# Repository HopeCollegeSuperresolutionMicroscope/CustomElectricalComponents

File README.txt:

#README

This Directory Serves To Store directions and specifications about electrical components of the microscope setup.

IMPORTANT Point about Schematics and EagleCAD:

	Schematics were created in EagleCAD free version.  These schematics make use of 3rd party libraries provided
        by sites like Element14 and handdrawn library parts based off of datasheets when not found.

	Opening a Schematic In EagleCAD:

		Since the free version of EagleCAD seems to limit all projects to the specific eagle/ folder designated
		 by the program on Install, it is recommended to move the schematic to this directory if intending to do 
		 work on the underlying schematic or pre-Gerber pcb board layout.

		In order to have access to the libraries, from the Eagle Control Panel: 
				Right click Libraries -> Library Manager
				Upper left Tab -> Available
				Browse -> Search for each library in EagleLibraries
				If the library is new it will be added in the Available dialog
				Click on the desired library and click Use button
				You should now see the library in the In Use Tab

Directory Layout:
	|
	|
	| ------- EagleLibraries/
	|		|	:Since Schematics were created in EagleCAD (freeware edition), additional libraries are housed here
	|		|
	|		|
	|		| ------- 3rdParty/ 
	|		|		: Part libraries that were imported from 3rd Party distributors.  See About.txt if wanting to look up revisions.
	|		|
	|		|
	|		| ------- HandCreated/
	|				: Parts that were created from Manufacturer DataSheets by individuals.  
	|				   Add the file name to Confirmed.txt when a pcb footprint has been used and verified.
	|
	|
	| ------- USB_TO_ILDA_Adapter/ 
	|		|	: Electronics for using ILDA device as a laser illumination source
	|		|
	|		|
	|		| ------- (Version) /
	|				|	:See About.txt for Version Different highlights
	|				|
	|				|
	|				| ------- Schematics/
	|				|		: Electrical Connection Schematics
	|				|
	|				|
	|				| ------- Gerber/
	|				|		: Gerber Files for PCBs that have been proven 
	|				|
	|				|
	|				| ------ DataSheets/
	|						: DataSheets Related to important components (ICs at the very least)
	|				
	|
	| ------ USB_TO_RS485_Connection/
	|		|	:Electronic connector and connections for RS-485 Comm with OrientalMotors CRPK
	|		|
	|		|
	|		| ------ Schematics/
	|		|		: Electrical Connections (Since this is a non-standard connection)
	|		|
	|		|
	|		| ------ DataSheets/
	|		|		: DataSheets related to important Components (motor controller and USB adapter)
	|		|
	|		|
	|		| ------ Figures/
	|				: Explanations for adapting the non-standard connection
	|		
	|
	| ------ Power_Supply/
			|	:Electrical connections for using Wall Power to provide stable voltage to OrientalMotors CRPK
			|
			|
			| ------ Schematics/
			|		: Electrical Connections (For pins to terminals etc.)
			|
			|
			| ------ DataSheets/ 
			|		: DataSheets related to important components
			|
			|
			| ------ Figures/
					:Explanation for making connections if there is a difficulty

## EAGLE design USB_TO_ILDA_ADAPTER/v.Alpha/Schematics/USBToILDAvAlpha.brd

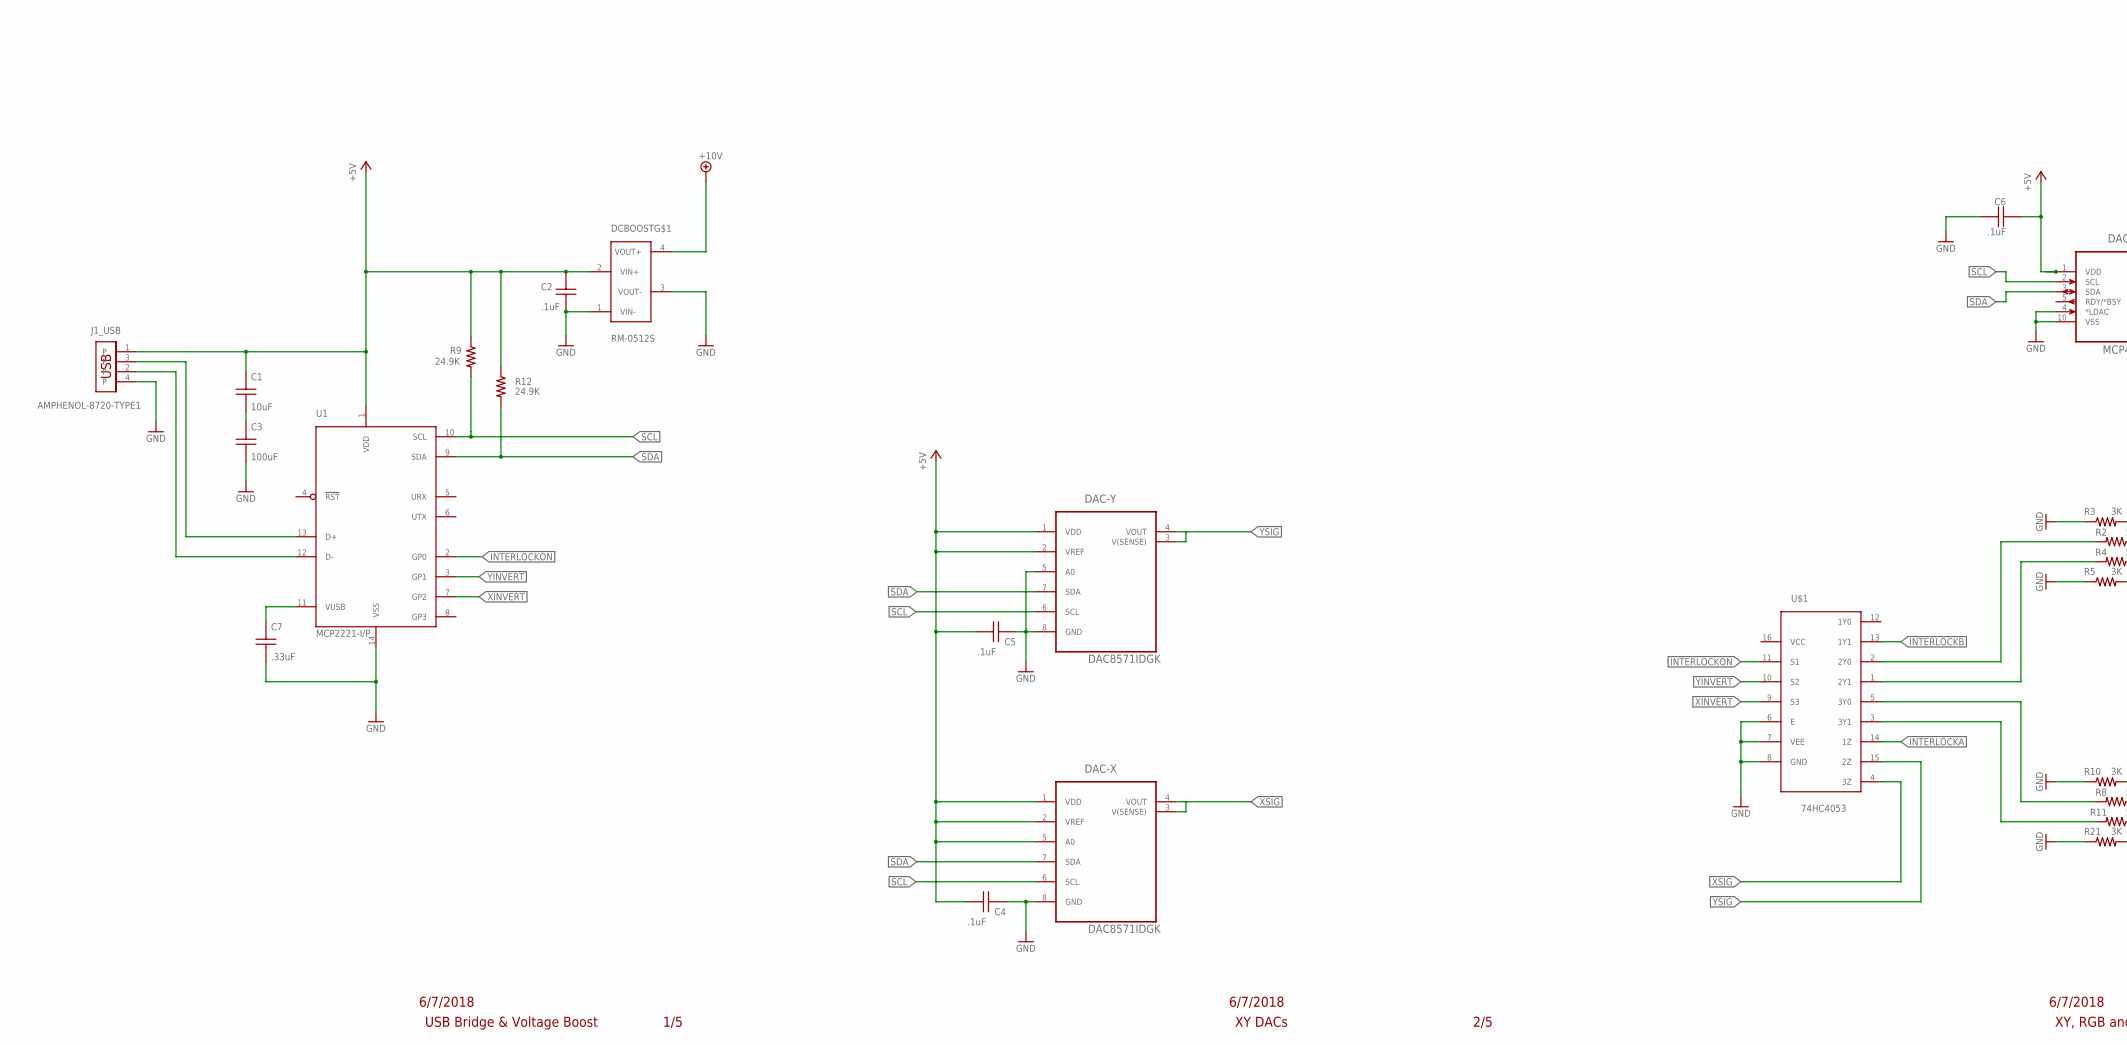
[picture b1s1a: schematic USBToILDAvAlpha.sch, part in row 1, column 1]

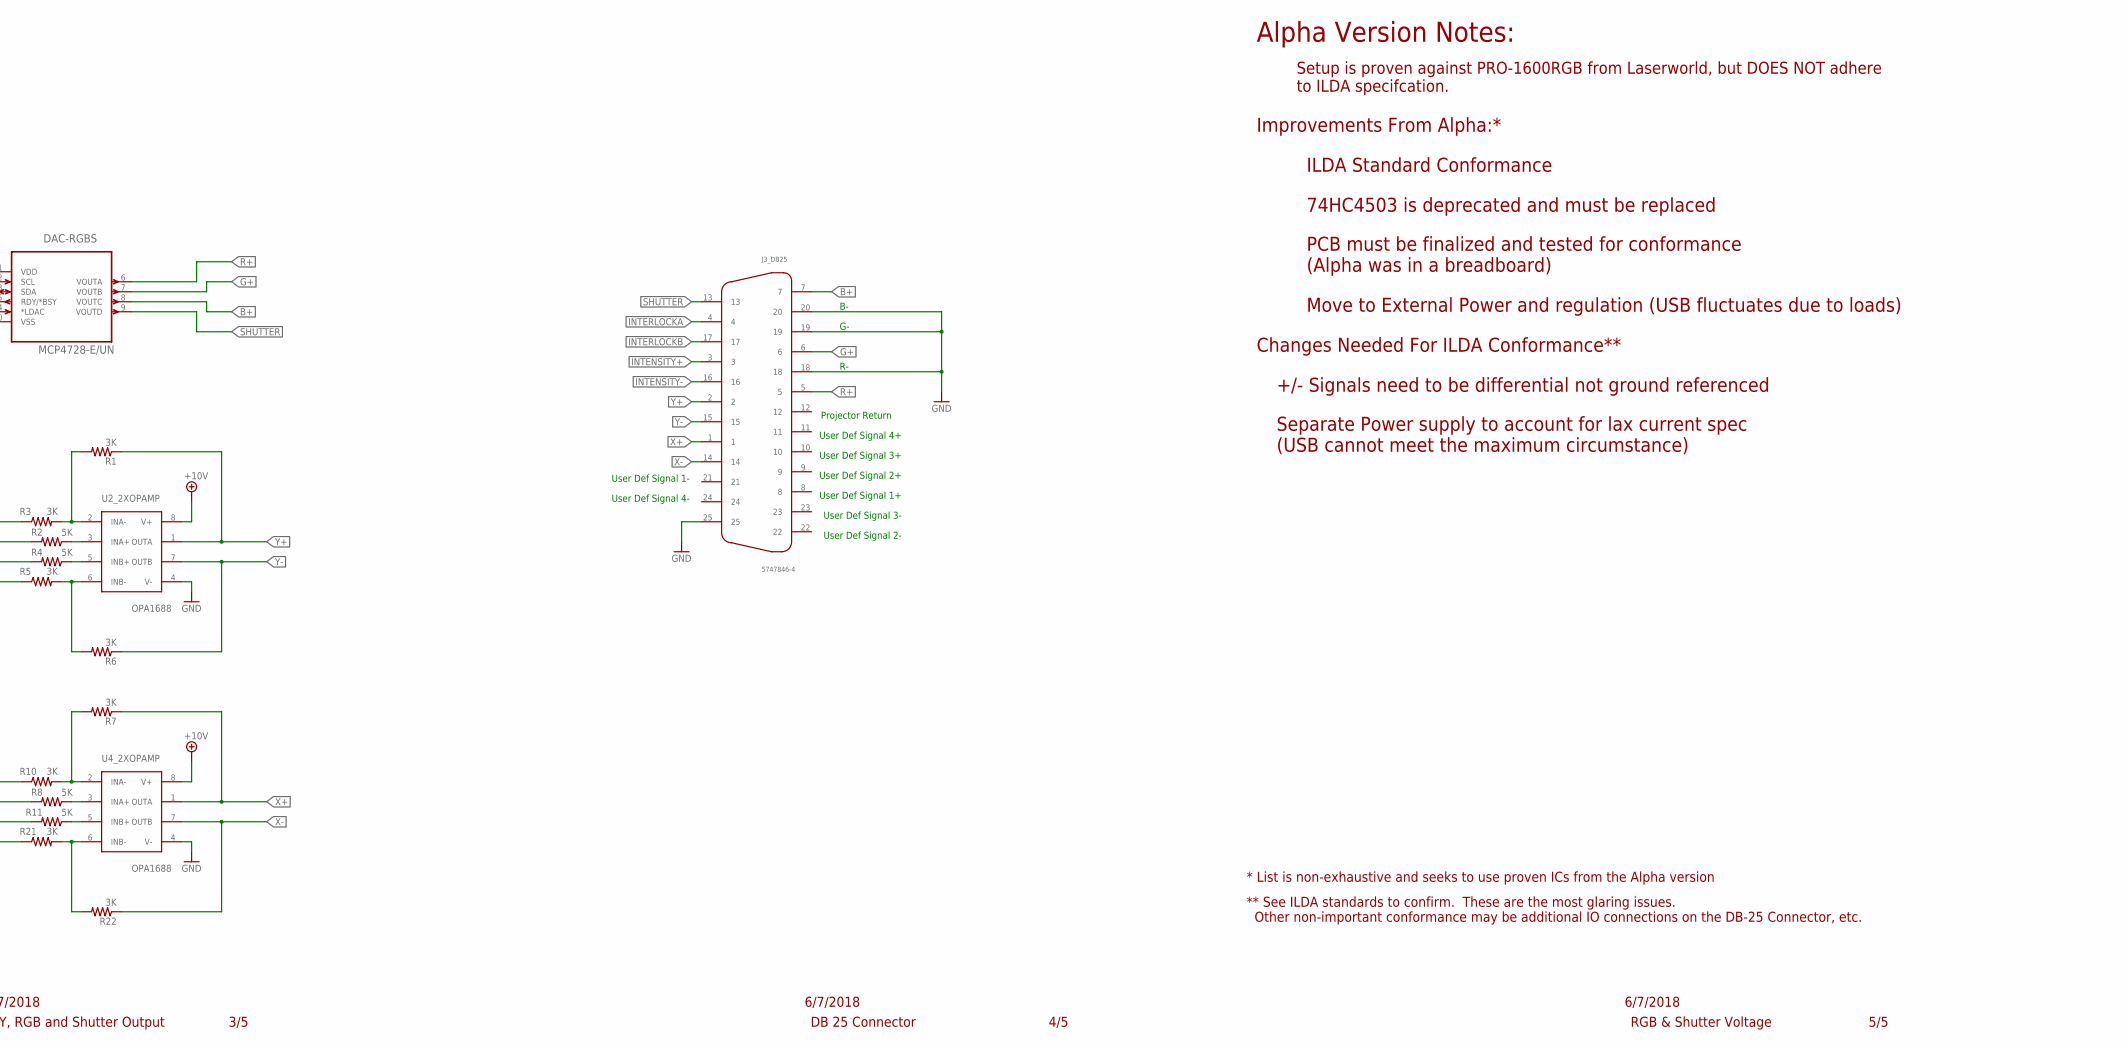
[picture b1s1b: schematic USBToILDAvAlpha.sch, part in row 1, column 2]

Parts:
C1: 10uF; WM1
C2, C4, C5, C6: .1uF; WM1
C3: 100uF; WM1
C7: .33uF; WM1
DAC-RGBS: MCP4728-E/UN; SOP50P490X110-10N
DAC-X: DAC8571IDGK; SOP65P490X110-8N
DAC-Y: DAC8571IDGK; SOP65P490X110-8N
DCBOOST: RM-0512S; SIP-4
J1_: AMPHENOL-8720-TYPE1; 87520
J3_: 5747846-4
R1, R3, R5, R6, R7, R10, R21, R22: 3K; R01005
R2, R4, R8, R11: 5K; R01005
R9, R12: 24.9K; R01005
U1: MCP2221-I/P; DIL14
U2, U4: OPA1688; SOIC-8
U$1: 74HC4053; SO16

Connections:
+5V: C1.P$1 (A), C2.P$1 (A), C4.P$1 (A), C5.P$1 (A), C6.P$2 (B), DAC-RGBS.1 (VDD), DAC-X.1 (VDD), DAC-X.2 (VREF), DAC-X.5 (A0), DAC-Y.1 (VDD), DAC-Y.2 (VREF), DCBOOST.2 (VIN+), J1_.1, R9.1, R12.1, U1.1 (VDD)
+9V: DCBOOST.4 (VOUT+)
+10V: U2.8 (V+), U4.8 (V+)
B+: DAC-RGBS.8 (VOUTC), J3_.7
G+: DAC-RGBS.7 (VOUTB), J3_.6
GND: C2.P$2 (B), C3.P$2 (B), C4.P$2 (B), C5.P$2 (B), C6.P$1 (A), C7.P$2 (B), DAC-RGBS.4 (*LDAC), DAC-RGBS.10 (VSS), DAC-X.8 (GND), DAC-Y.5 (A0), DAC-Y.8 (GND), DCBOOST.1 (VIN-), DCBOOST.3 (VOUT-), J1_.4, J3_.18, J3_.19, J3_.20, J3_.25, R3.1, R5.1, R10.1, R21.1, U1.14 (VSS), U2.4 (V-), U4.4 (V-), U$1.6 (E), U$1.7 (VEE), U$1.8 (GND)
INTENSITY+: J3_.3
INTENSITY-: J3_.16
INTERLOCKA: J3_.4, U$1.14 (1Z)
INTERLOCKB: J3_.17, U$1.13 (1Y1)
INTERLOCKON: U1.2 (GP0), U$1.11 (S1)
unnamed: C1.P$2 (B), C3.P$1 (A)
unnamed: J1_.2, U1.12 (D-)
unnamed: J1_.3, U1.13 (D+)
unnamed: R1.2, R3.2, U2.2 (INA-)
unnamed: R2.1, U2.3 (INA+)
unnamed: R2.2, U$1.2 (2Y0)
unnamed: R7.2, R10.2, U4.2 (INA-)
unnamed: R8.1, U4.3 (INA+)
unnamed: R8.2, U$1.5 (3Y0)
unnamed: R4.2, U$1.1 (2Y1)
unnamed: R4.1, U2.5 (INB+)
unnamed: R11.2, U$1.3 (3Y1)
unnamed: R5.2, R6.2, U2.6 (INB-)
unnamed: C7.P$1 (A), U1.11 (VUSB)
unnamed: R11.1, U4.5 (INB+)
unnamed: R21.2, R22.2, U4.6 (INB-)
R+: DAC-RGBS.6 (VOUTA), J3_.5
SCL: DAC-RGBS.2 (SCL), DAC-X.6 (SCL), DAC-Y.6 (SCL), R9.2, U1.10 (SCL)
SDA: DAC-RGBS.3 (SDA), DAC-X.7 (SDA), DAC-Y.7 (SDA), R12.2, U1.9 (SDA)
SHUTTER: J3_.13
X+: J3_.1, R7.1, U4.1 (OUTA)
X-: J3_.14, R22.1, U4.7 (OUTB)
XINVERT: U1.7 (GP2), U$1.9 (S3)
XSIG: DAC-X.3 (V(SENSE)), DAC-X.4 (VOUT), U$1.4 (3Z)
Y+: J3_.2, R1.1, U2.1 (OUTA)
Y-: J3_.15, R6.1, U2.7 (OUTB)
YINVERT: U1.3 (GP1), U$1.10 (S2)
YSIG: DAC-Y.3 (V(SENSE)), DAC-Y.4 (VOUT), U$1.15 (2Z)

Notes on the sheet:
User Def Signal 1+
User Def Signal 2+
User Def Signal 3+
User Def Signal 4+
Projector Return
User Def Signal 1-
User Def Signal 2-
User Def Signal 3-
User Def Signal 4-
6/7/2018
RGB & Shutter Voltage
4/5
DB 25 Connector
5/5
USB Bridge & Voltage Boost
1/5
XY, RGB and Shutter Output
3/5
XY DACs
2/5
Alpha Version Notes:
Setup is proven against PRO-1600RGB from Laserworld, but DOES NOT adhere to ILDA specifcation.
Changes Needed For ILDA Conformance**
+/- Signals need to be differential not ground referenced
Separate Power supply to account for lax current spec (USB cannot meet the maximum circumstance)
Improvements From Alpha:*
ILDA Standard Conformance
74HC4503 is deprecated and must be replaced
PCB must be finalized and tested for conformance (Alpha was in a breadboard)
Move to External Power and regulation (USB fluctuates due to loads)
* List is non-exhaustive and seeks to use proven ICs from the Alpha version
** See ILDA standards to confirm. These are the most glaring issues. Other non-important conformance may be additional IO connections on the DB-25 Connector, etc.

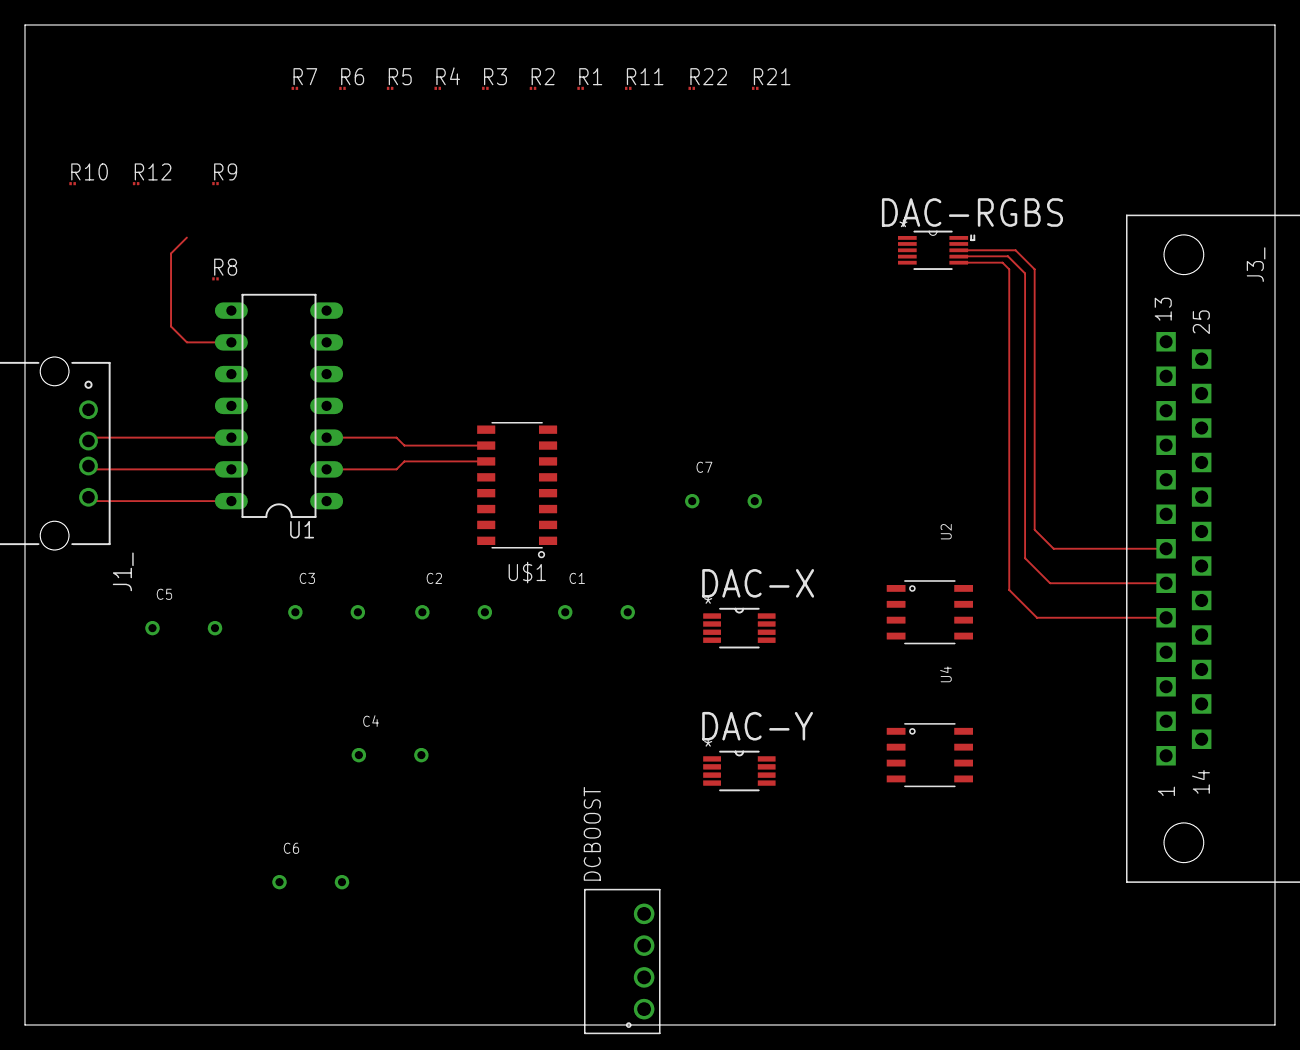
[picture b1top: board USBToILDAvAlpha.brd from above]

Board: 2 copper layers, 100.0 x 80.0 mm, 31 parts (0 on the bottom side), 35 nets.

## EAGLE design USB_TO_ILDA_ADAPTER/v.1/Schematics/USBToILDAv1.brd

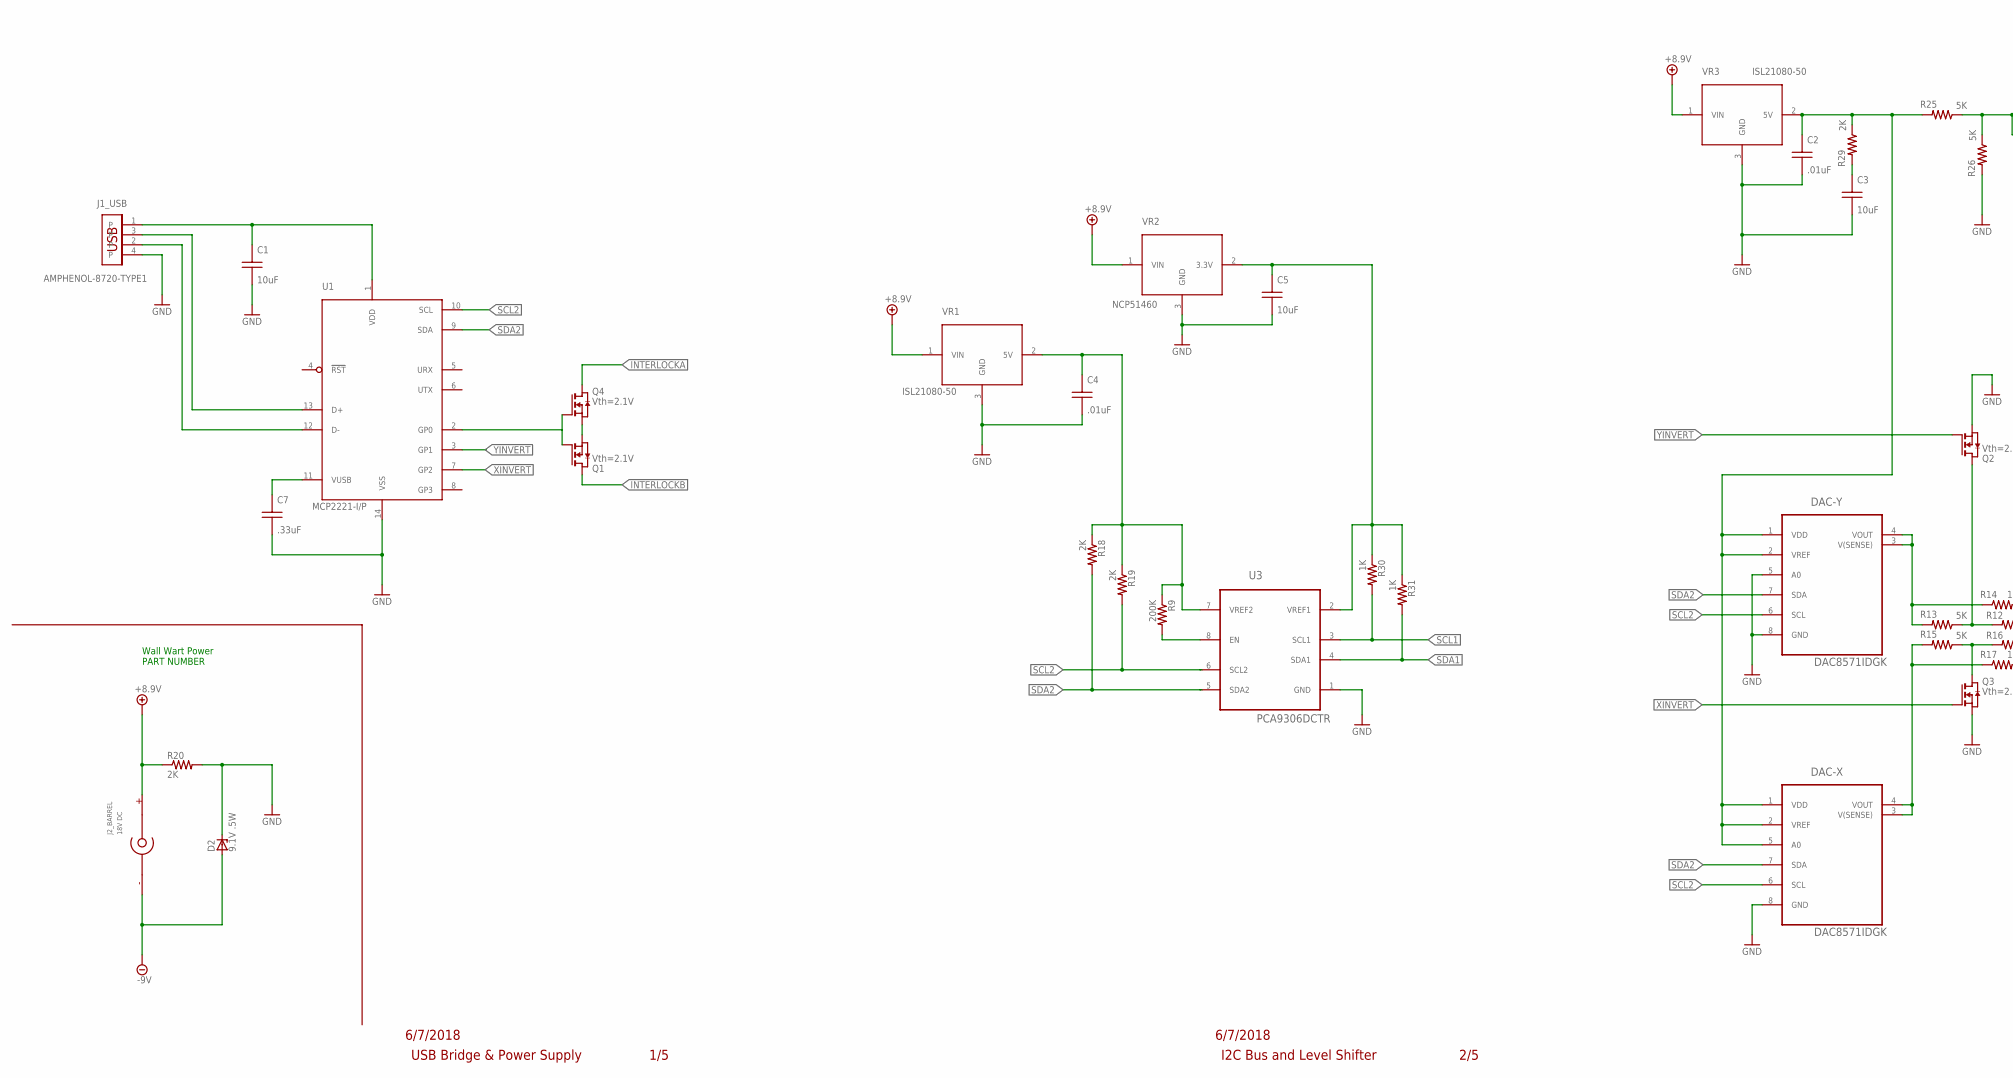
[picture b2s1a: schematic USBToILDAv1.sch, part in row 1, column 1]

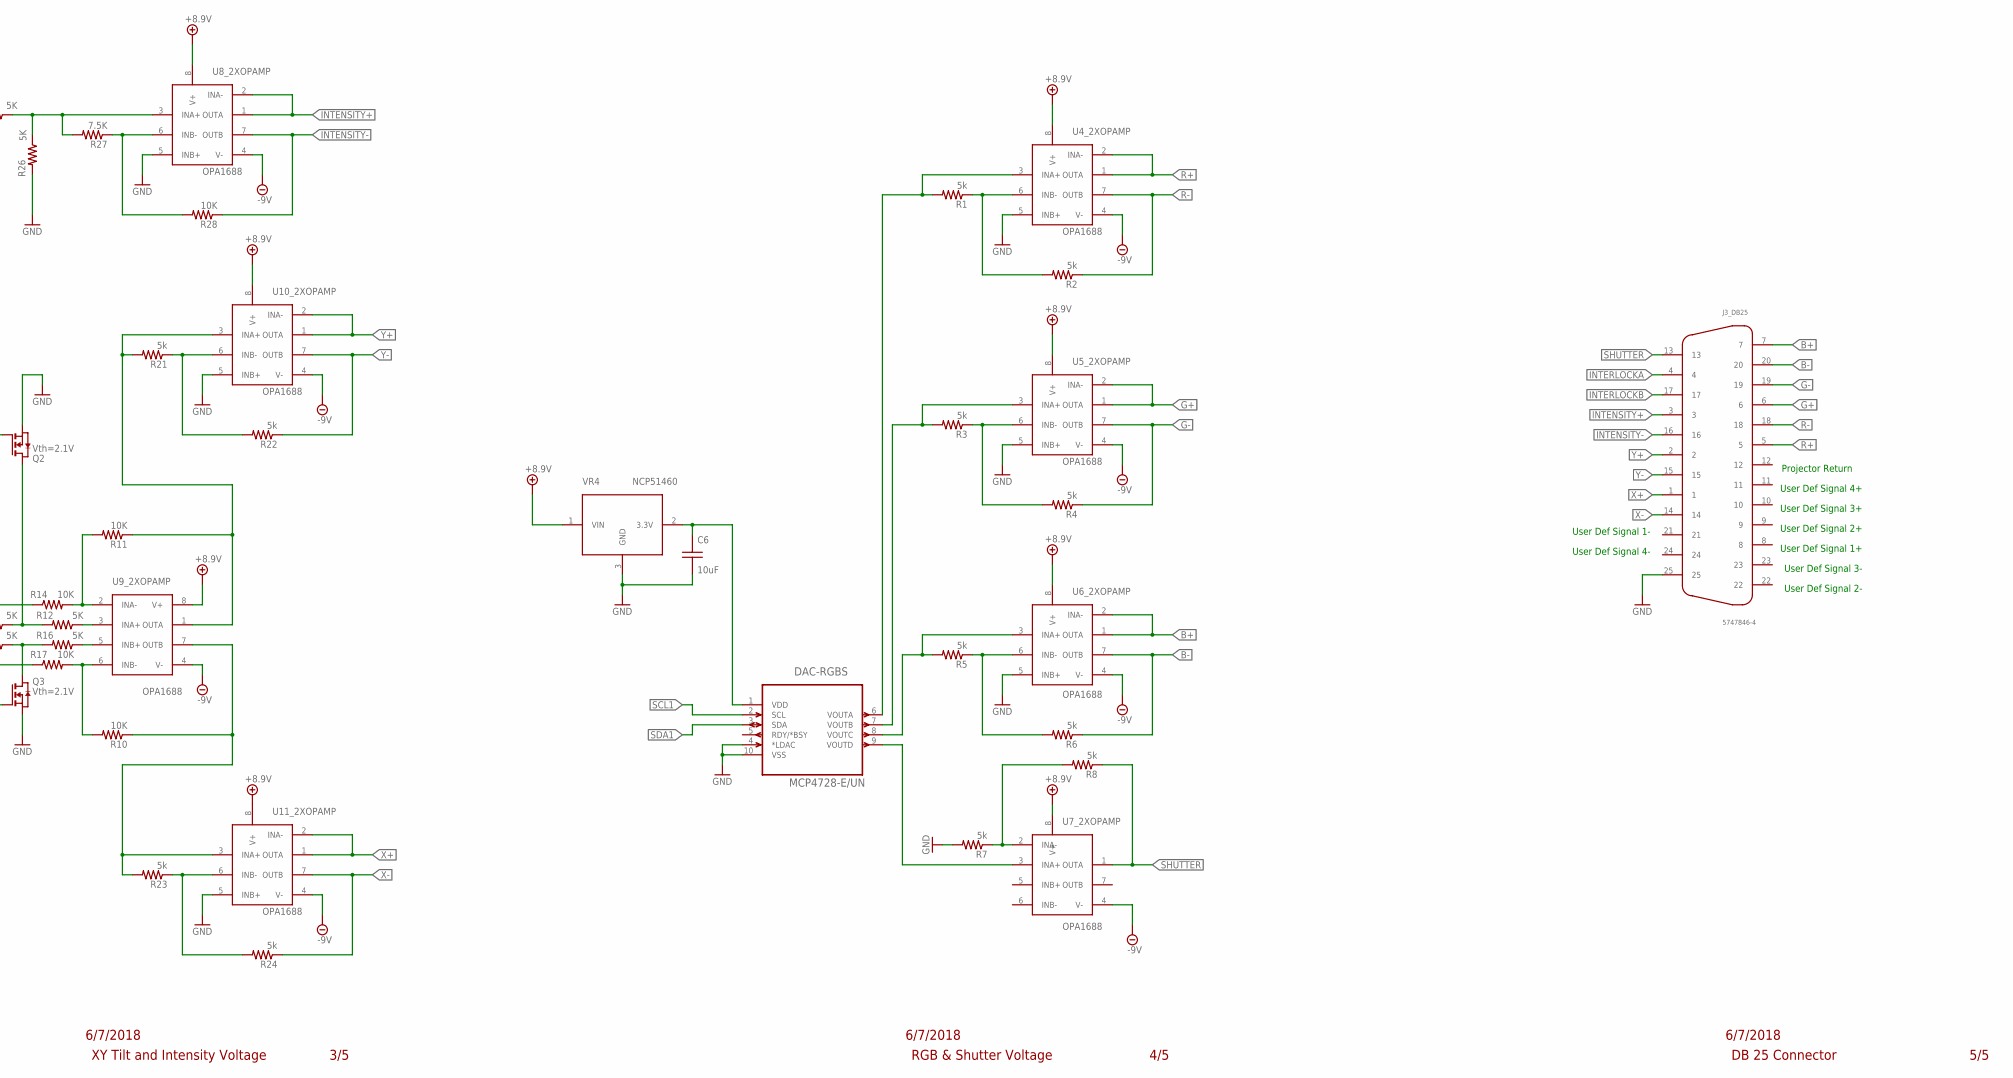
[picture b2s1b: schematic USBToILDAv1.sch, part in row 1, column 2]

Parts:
C1, C3, C5, C6: 10uF; WM1
C2, C4: .01uF; WM1
C7: .33uF; WM1
D2: 9.1V .5W; DO35Z10
DAC-RGBS: MCP4728-E/UN; SOP50P490X110-10N
DAC-X: DAC8571IDGK; SOP65P490X110-8N
DAC-Y: DAC8571IDGK; SOP65P490X110-8N
J1_: AMPHENOL-8720-TYPE1; 87520
J2_BARREL: 18V DC; PJ-036AH-SMT-TR
J3_: 5747846-4
Q1, Q2, Q3, Q4: Vth=2.1V; SOT-26
R1, R2, R3, R4, R5, R6, R7, R8, R21, R22, R23, R24: 5k; R01005
R9: 200K; R01005
R10, R11, R14, R17, R28: 10K; R01005
R12, R13, R15, R16, R25, R26: 5K; R01005
R18, R19, R20, R29: 2K; R01005
R27: 7.5K; R01005
R30, R31: 1K; R01005
U1: MCP2221-I/P; DIL14
U3: PCA9306DCTR; SOP65P400X130-8N
U4, U5, U6, U7, U8, U9, U10, U11: OPA1688; SOIC-8
VR1, VR3: ISL21080-50; SOT23-CASE308
VR2, VR4: NCP51460; SOT-23-CASE318

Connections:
+8.9V: J2_BARREL.1 (+), R20.1, U4.8 (V+), U5.8 (V+), U6.8 (V+), U7.8 (V+), U8.8 (V+), U9.8 (V+), U10.8 (V+), U11.8 (V+), VR1.1 (VIN), VR2.1 (VIN), VR3.1 (VIN), VR4.1 (VIN)
-9V: D2.A, J2_BARREL.2 (-), J2_BARREL.3 (-), U4.4 (V-), U5.4 (V-), U6.4 (V-), U7.4 (V-), U8.4 (V-), U9.4 (V-), U10.4 (V-), U11.4 (V-)
B+: J3_.7, U6.1 (OUTA), U6.2 (INA-)
B-: J3_.20, R6.1, U6.7 (OUTB)
G+: J3_.6, U5.1 (OUTA), U5.2 (INA-)
G-: J3_.19, R4.1, U5.7 (OUTB)
GND: C2.P$2 (B), C3.P$2 (B), C4.P$2 (B), C5.P$2 (B), C6.P$2 (B), C7.P$2 (B), D2.C, DAC-RGBS.4 (*LDAC), DAC-RGBS.10 (VSS), DAC-X.8 (GND), DAC-Y.5 (A0), DAC-Y.8 (GND), J1_.4, J3_.25, Q2.S, Q3.S, R7.2, R20.2, R26.2, U1.14 (VSS), U3.1 (GND), U4.5 (INB+), U5.5 (INB+), U6.5 (INB+), U8.5 (INB+), U10.5 (INB+), U11.5 (INB+), VR1.3 (GND), VR2.3 (GND), VR3.3 (GND), VR4.3 (GND)
INTENSITY+: J3_.3, U8.1 (OUTA), U8.2 (INA-)
INTENSITY-: J3_.16, R28.1, U8.7 (OUTB)
INTERLOCK-I/O: Q1.G, Q4.G, U1.2 (GP0)
INTERLOCKA: J3_.4, Q4.D1 (D), Q4.D2 (D), Q4.D3 (D), Q4.D4 (D)
INTERLOCKB: J3_.17, Q1.D1 (D), Q1.D2 (D), Q1.D3 (D), Q1.D4 (D)
unnamed: J1_.2, U1.12 (D-)
unnamed: J1_.3, U1.13 (D+)
unnamed: C1.P$1 (A), J1_.1, U1.1 (VDD)
unnamed: R9.2, U3.8 (EN)
unnamed: DAC-RGBS.6 (VOUTA), R1.2, U4.3 (INA+)
unnamed: R7.1, R8.2, U7.2 (INA-)
unnamed: R1.1, R2.2, U4.6 (INB-)
unnamed: C6.P$1 (A), DAC-RGBS.1 (VDD), VR4.2 (3.3V)
unnamed: DAC-RGBS.7 (VOUTB), R3.2, U5.3 (INA+)
unnamed: R25.1, R26.1, R27.2, U8.3 (INA+)
unnamed: R3.1, R4.2, U5.6 (INB-)
unnamed: C2.P$1 (A), DAC-X.1 (VDD), DAC-X.2 (VREF), DAC-X.5 (A0), DAC-Y.1 (VDD), DAC-Y.2 (VREF), R25.2, R29.1, VR3.2 (5V)
unnamed: DAC-RGBS.8 (VOUTC), R5.2, U6.3 (INA+)
unnamed: R11.1, R21.2, U9.1 (OUTA), U10.3 (INA+)
unnamed: R5.1, R6.2, U6.6 (INB-)
unnamed: C7.P$1 (A), U1.11 (VUSB)
unnamed: DAC-RGBS.9 (VOUTD), U7.3 (INA+)
unnamed: C4.P$1 (A), R9.1, R18.1, R19.1, U3.7 (VREF2), VR1.2 (5V)
unnamed: Q1.S, Q4.S
unnamed: R11.2, R14.2, U9.2 (INA-)
unnamed: R12.1, U9.3 (INA+)
unnamed: Q2.D1 (D), Q2.D2 (D), Q2.D3 (D), Q2.D4 (D), R12.2, R13.1
unnamed: DAC-Y.3 (V(SENSE)), DAC-Y.4 (VOUT), R13.2, R14.1
unnamed: DAC-X.3 (V(SENSE)), DAC-X.4 (VOUT), R15.2, R17.1
unnamed: Q3.D1 (D), Q3.D2 (D), Q3.D3 (D), Q3.D4 (D), R15.1, R16.2
unnamed: R16.1, U9.5 (INB+)
unnamed: R10.2, R17.2, U9.6 (INB-)
unnamed: R10.1, R23.2, U9.7 (OUTB), U11.3 (INA+)
unnamed: C3.P$1 (A), R29.2
unnamed: R21.1, R22.2, U10.6 (INB-)
unnamed: R23.1, R24.2, U11.6 (INB-)
unnamed: R27.1, R28.2, U8.6 (INB-)
unnamed: C5.P$1 (A), R30.1, R31.1, U3.2 (VREF1), VR2.2 (3.3V)
R+: J3_.5, U4.1 (OUTA), U4.2 (INA-)
R-: J3_.18, R2.1, U4.7 (OUTB)
SCL1: DAC-RGBS.2 (SCL), R30.2, U3.3 (SCL1)
SCL2: DAC-X.6 (SCL), DAC-Y.6 (SCL), R19.2, U1.10 (SCL), U3.6 (SCL2)
SDA1: DAC-RGBS.3 (SDA), R31.2, U3.4 (SDA1)
SDA2: DAC-X.7 (SDA), DAC-Y.7 (SDA), R18.2, U1.9 (SDA), U3.5 (SDA2)
SHUTTER: J3_.13, R8.1, U7.1 (OUTA)
X+: J3_.1, U11.1 (OUTA), U11.2 (INA-)
X-: J3_.14, R24.1, U11.7 (OUTB)
XINVERT: Q3.G, U1.7 (GP2)
Y+: J3_.2, U10.1 (OUTA), U10.2 (INA-)
Y-: J3_.15, R22.1, U10.7 (OUTB)
YINVERT: Q2.G, U1.3 (GP1)

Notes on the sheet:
User Def Signal 1+
User Def Signal 2+
User Def Signal 3+
User Def Signal 4+
Projector Return
User Def Signal 1-
User Def Signal 2-
User Def Signal 3-
User Def Signal 4-
Wall Wart Power PART NUMBER
6/7/2018
RGB & Shutter Voltage
4/5
DB 25 Connector
5/5
USB Bridge & Power Supply
1/5
XY Tilt and Intensity Voltage
3/5
I2C Bus and Level Shifter
2/5

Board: 2 copper layers, 63 parts (0 on the bottom side), 58 nets, no tracks yet.

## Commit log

2019-07-22 Initial Commit of bread-boarded alpha, and to be tested v1
2019-07-22 Added DataSheet for the RS485 Adapter, the connection instruction pdf, and appropriate about text.
2019-08-20 Added instructions for creating an insulated and accessible power supply box
2019-08-20 Pdf of schematic for accessibility
